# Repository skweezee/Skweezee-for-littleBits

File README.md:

# Skweezee-for-littleBits
Skweezee expansion kit for littleBits

All components of the extension kit for littleBits are available as open source hardware (licensed under CC BY-SA 4.0) and software (copyrighted by KU Leuven and licensed under MIT license).

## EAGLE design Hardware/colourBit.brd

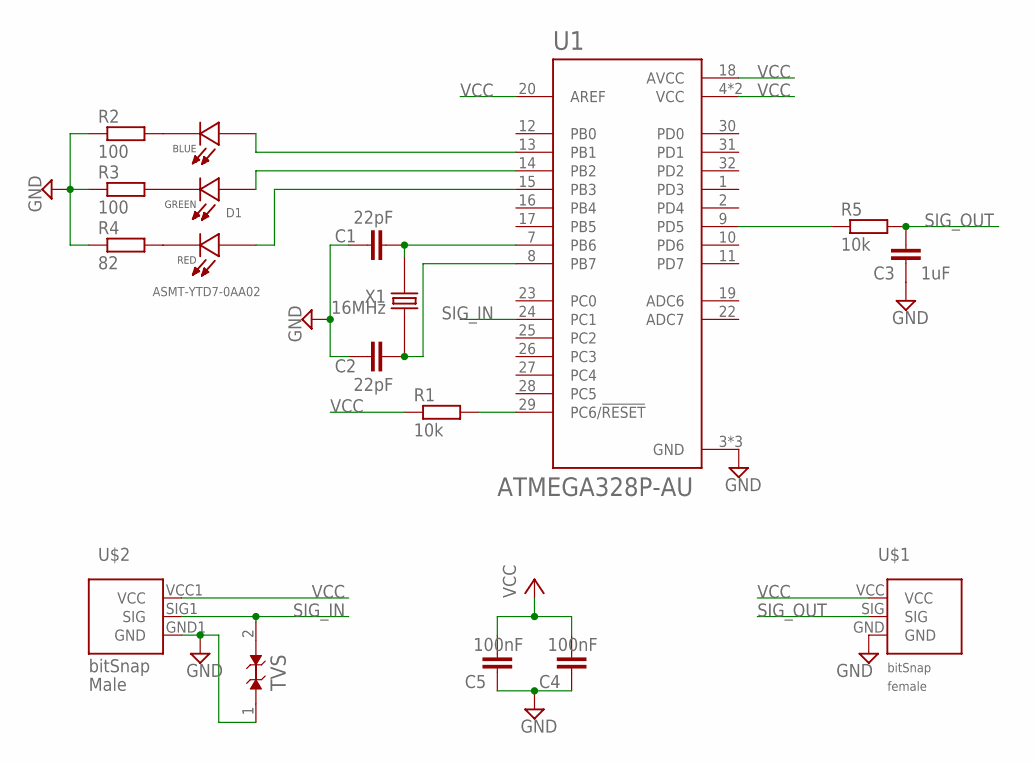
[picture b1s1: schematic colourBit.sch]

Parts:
C1, C2: 22pF; C0805
C3: 1uF; C0805
C4, C5: 100nF; C0805
D1: ASMT-YTD7-0AA02; LED_ASMT-YTD7-0AA02
R1, R5: 10k; R0805
R2, R3: 100; R0805
R4: 82; R0805
TVS: ESD9B5.0ST5G; SODFL1006X40N
U1: ATMEGA328P-AU; QFP80P900X900X120-32N
U$1: BITSNAP_V03_FEMALE
U$2: BITSNAP_V03_MALE
X1: 16MHz; XTAL500X320X120

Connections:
GND: C1.1, C2.1, C3.1, C4.1, C5.1, R2.1, R3.1, R4.1, TVS.1 (A), U1.3 (GND), U1.5 (GND), U1.21 (GND), U$1.GND, U$2.GND1 (GND)
unnamed: C1.2, U1.7 (PB6), X1.2
unnamed: C2.2, U1.8 (PB7), X1.1
unnamed: R1.2, U1.29 (PC6/!RESET)
unnamed: D1.1 (B_C), R2.2
unnamed: D1.2 (G_C), R3.2
unnamed: D1.3 (R_C), R4.2
unnamed: D1.6 (B_A), U1.13 (PB1)
unnamed: D1.5 (G_A), U1.14 (PB2)
unnamed: D1.4 (R_A), U1.15 (PB3)
unnamed: R5.1, U1.9 (PD5)
SIG_IN: TVS.2 (A1), U1.24 (PC1), U$2.SIG1 (SIG)
SIG_OUT: C3.2, R5.2, U$1.SIG
VCC: C4.2, C5.2, R1.1, U1.4 (VCC), U1.6 (VCC), U1.18 (AVCC), U1.20 (AREF), U$1.VCC, U$2.VCC1 (VCC)

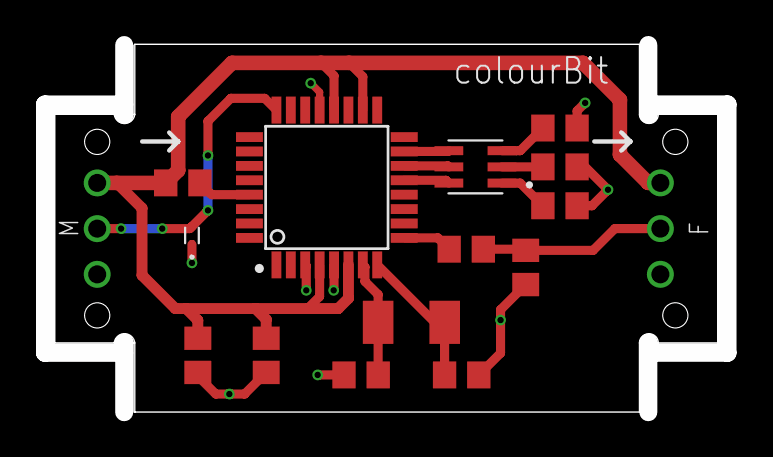
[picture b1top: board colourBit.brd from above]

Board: 2 copper layers, 37.9 x 20.4 mm, 16 parts (0 on the bottom side), 14 nets.

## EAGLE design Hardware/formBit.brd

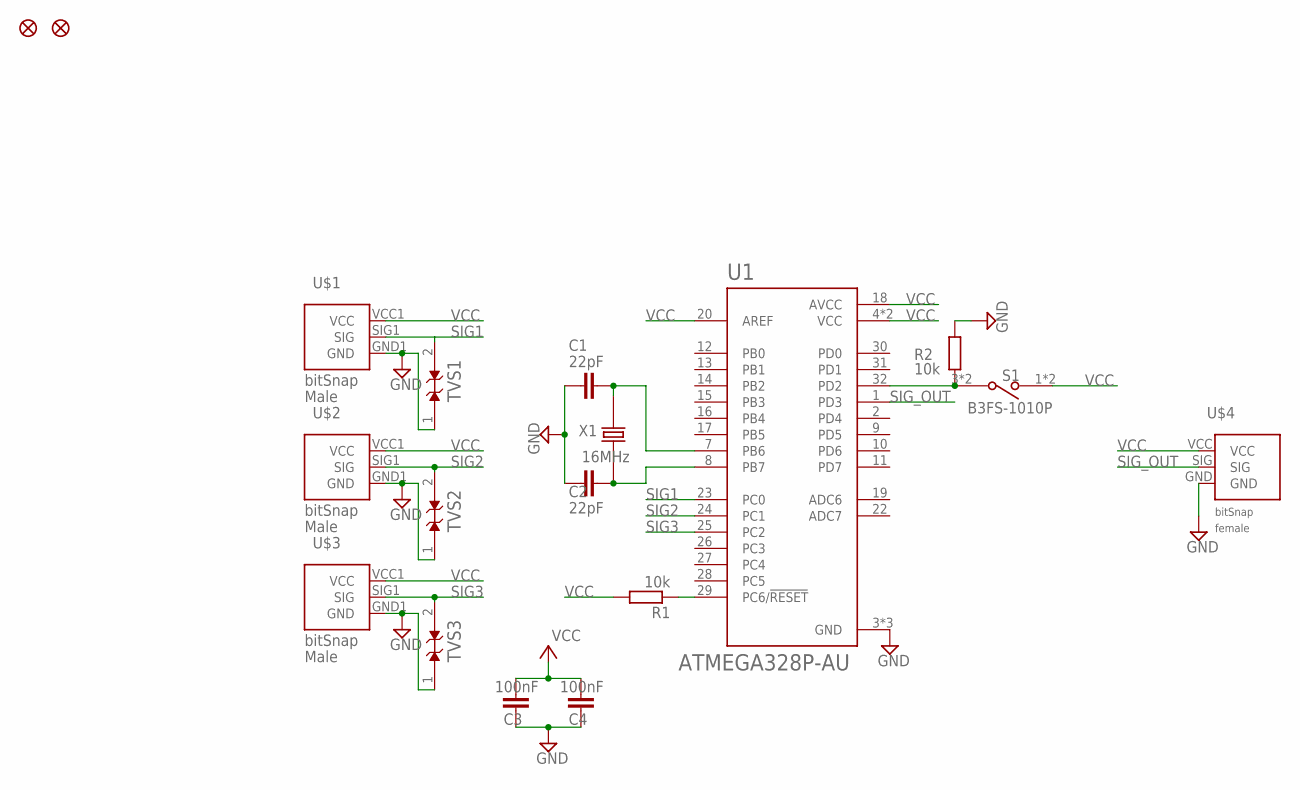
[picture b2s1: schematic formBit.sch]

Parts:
C1, C2: 22pF; C0805
C3, C4: 100nF; C0805
R1, R2: 10k; R0805
S1: B3FS-1010P; SW_B3FS-1010P
TVS1, TVS2, TVS3: ESD9B5.0ST5G; SODFL1006X40N
U1: ATMEGA328P-AU; QFP80P900X900X120-32N
U$1, U$2, U$3: BITSNAP_V03_MALE
U$4: BITSNAP_V03_FEMALE
U$5, U$6: FIDUCIAL; FIDUCIAL1X2.5
X1: 16MHz; XTAL500X320X120

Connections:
GND: C1.1, C2.1, C3.1, C4.1, R2.1, TVS1.1 (A), TVS2.1 (A), TVS3.1 (A), U1.3 (GND), U1.5 (GND), U1.21 (GND), U$1.GND1 (GND), U$2.GND1 (GND), U$3.GND1 (GND), U$4.GND
unnamed: R2.2, S1.3 (2), S1.4 (2), U1.32 (PD2)
unnamed: C2.2, U1.8 (PB7), X1.1
unnamed: C1.2, U1.7 (PB6), X1.2
unnamed: R1.1, U1.29 (PC6/!RESET)
SIG1: TVS1.2 (A1), U1.23 (PC0), U$1.SIG1 (SIG)
SIG2: TVS2.2 (A1), U1.24 (PC1), U$2.SIG1 (SIG)
SIG3: TVS3.2 (A1), U1.25 (PC2), U$3.SIG1 (SIG)
SIG_OUT: U1.1 (PD3), U$4.SIG
VCC: C3.2, C4.2, R1.2, S1.1, S1.2 (1), U1.4 (VCC), U1.6 (VCC), U1.18 (AVCC), U1.20 (AREF), U$1.VCC1 (VCC), U$2.VCC1 (VCC), U$3.VCC1 (VCC), U$4.VCC

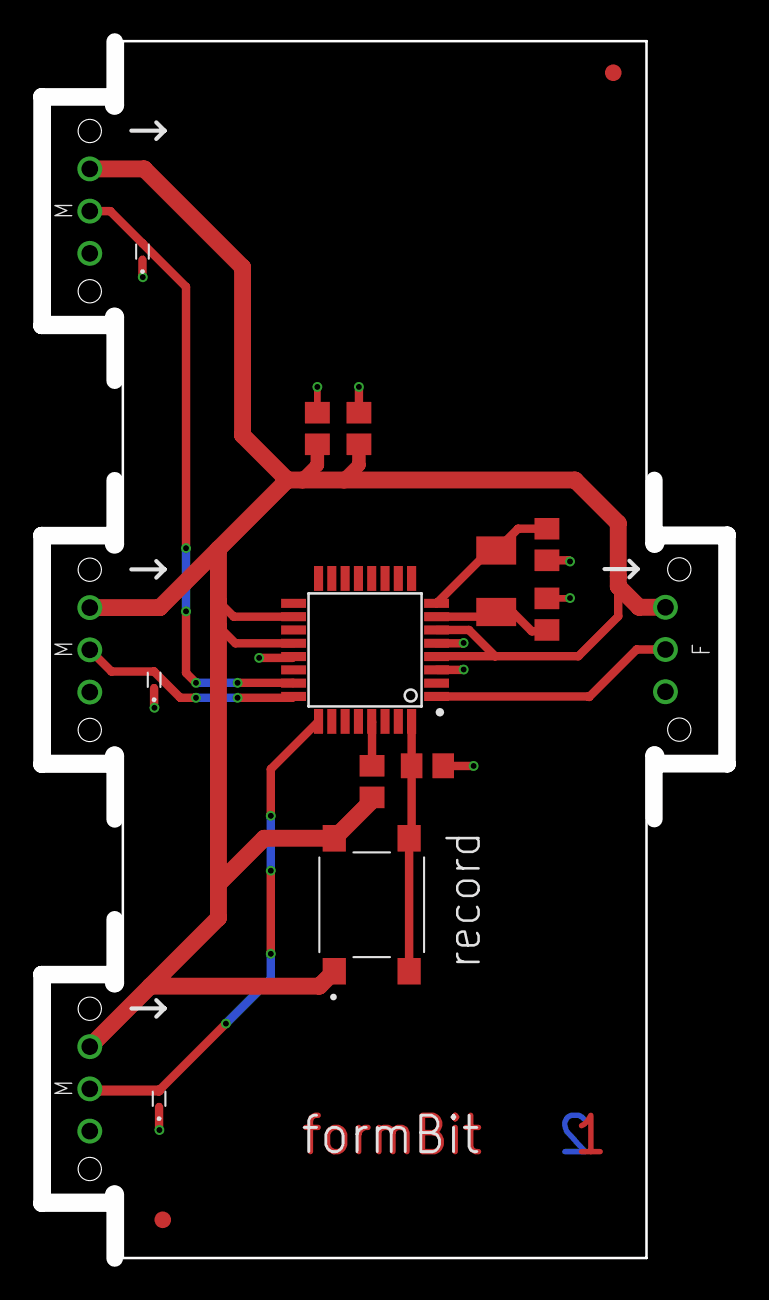
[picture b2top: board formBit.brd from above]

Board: 2 copper layers, 40.3 x 73.2 mm, 18 parts (0 on the bottom side), 10 nets.

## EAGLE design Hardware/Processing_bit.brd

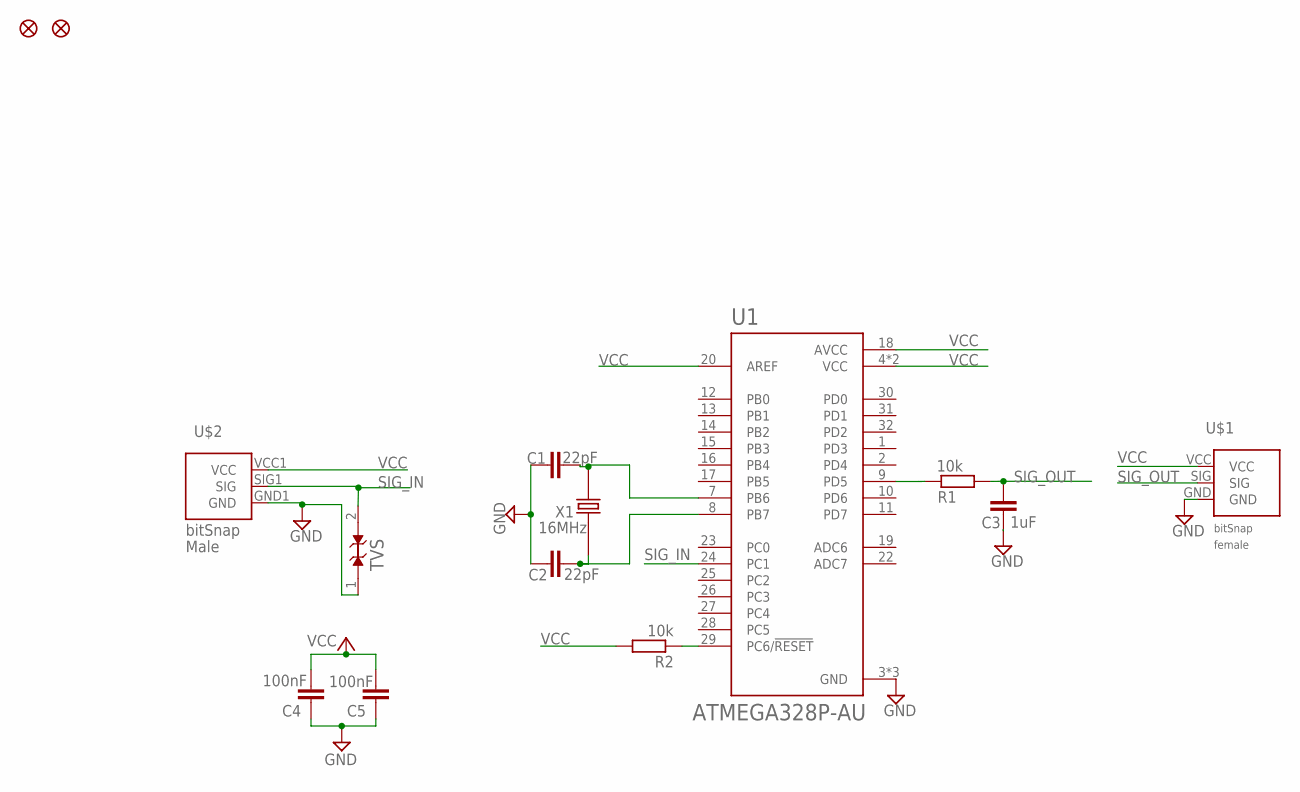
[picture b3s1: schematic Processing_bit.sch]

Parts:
C1, C2: 22pF; C0805
C3: 1uF; C0805
C4, C5: 100nF; C0805
R1, R2: 10k; R0805
TVS: ESD9B5.0ST5G; SODFL1006X40N
U1: ATMEGA328P-AU; QFP80P900X900X120-32N
U$1: BITSNAP_V03_FEMALE
U$2: BITSNAP_V03_MALE
U$3, U$4: FIDUCIAL; FIDUCIAL1X2.5
X1: 16MHz; XTAL500X320X120

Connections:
GND: C1.1, C2.1, C3.1, C4.1, C5.1, TVS.1 (A), U1.3 (GND), U1.5 (GND), U1.21 (GND), U$1.GND, U$2.GND1 (GND)
unnamed: C1.2, U1.7 (PB6), X1.2
unnamed: C2.2, U1.8 (PB7), X1.1
unnamed: R2.1, U1.29 (PC6/!RESET)
unnamed: R1.2, U1.9 (PD5)
SIG_IN: TVS.2 (A1), U1.24 (PC1), U$2.SIG1 (SIG)
SIG_OUT: C3.2, R1.1, U$1.SIG
VCC: C4.2, C5.2, R2.2, U1.4 (VCC), U1.6 (VCC), U1.18 (AVCC), U1.20 (AREF), U$1.VCC, U$2.VCC1 (VCC)

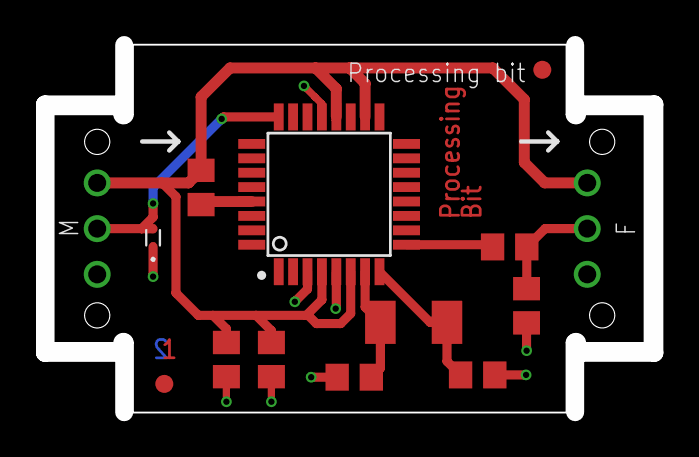
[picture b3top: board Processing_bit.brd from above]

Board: 2 copper layers, 33.9 x 20.4 mm, 14 parts (0 on the bottom side), 8 nets.

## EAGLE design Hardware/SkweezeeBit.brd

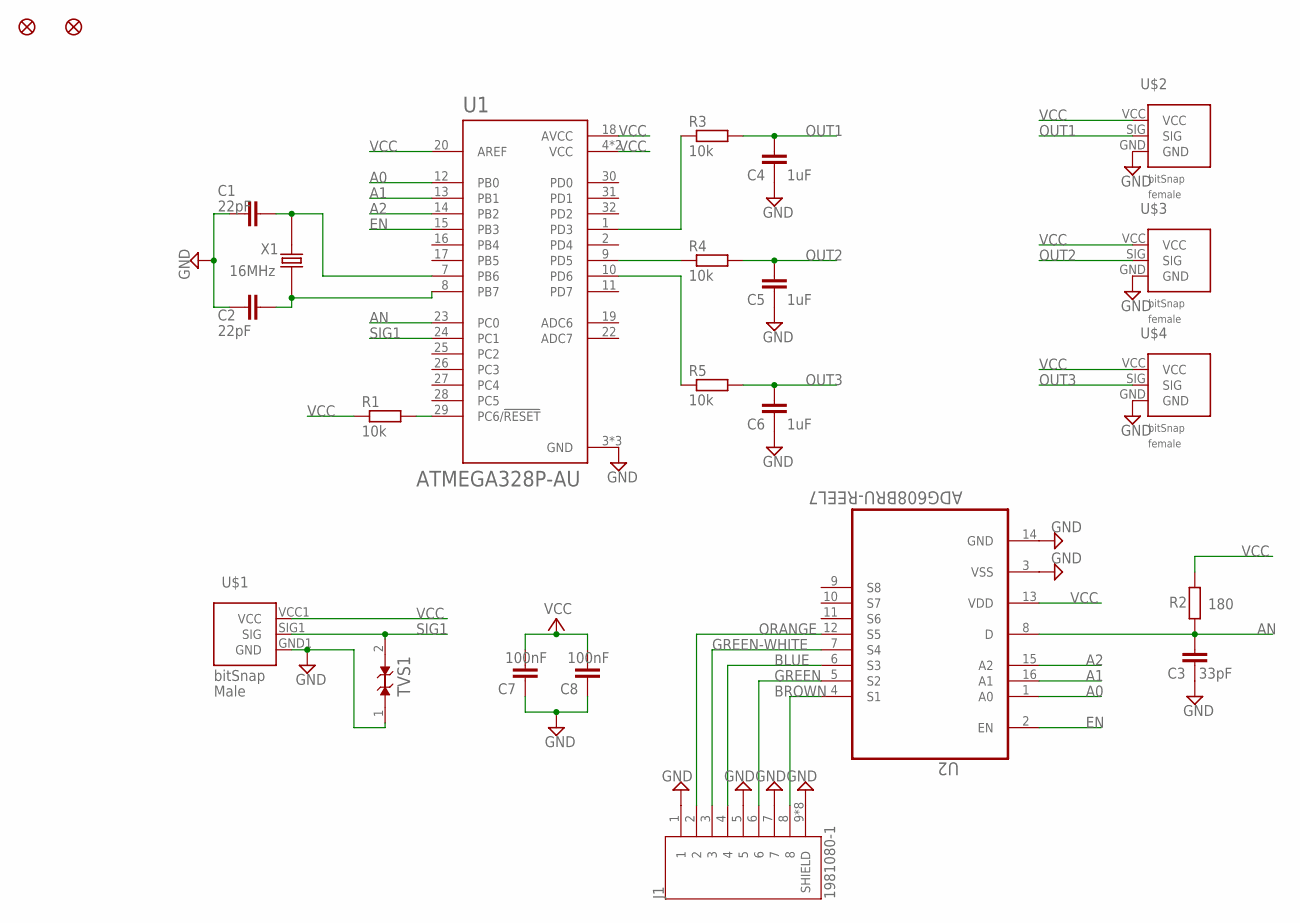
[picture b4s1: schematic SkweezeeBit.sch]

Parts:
C1, C2: 22pF; C0805
C3: 33pF; C0805
C4, C5, C6: 1uF; C0805
C7, C8: 100nF; C0805
J1: 1981080-1; CONN_1981080-1
R1, R3, R4, R5: 10k; R0805
R2: 180; R0805
TVS1: ESD9B5.0ST5G; SODFL1006X40N
U1: ATMEGA328P-AU; QFP80P900X900X120-32N
U2: ADG608BRU-REEL7; SOP65P640X120-16N
U$1: BITSNAP_V03_MALE
U$2, U$3, U$4: BITSNAP_V03_FEMALE
U$5, U$6: FIDUCIAL; FIDUCIAL1X2.5
X1: 16MHz; XTAL500X320X120

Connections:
A0: U1.12 (PB0), U2.1 (A0)
A1: U1.13 (PB1), U2.16 (A1)
A2: U1.14 (PB2), U2.15 (A2)
AN: C3.2, R2.1, U1.23 (PC0), U2.8 (D)
BLUE: J1.4, U2.6 (S3)
BROWN: J1.8, U2.4 (S1)
EN: U1.15 (PB3), U2.2 (EN)
GND: C1.1, C2.1, C3.1, C4.1, C5.1, C6.1, C7.1, C8.1, J1.1, J1.5, J1.7, J1.9 (SHIELD), J1.9.1 (SHIELD), J1.10 (SHIELD), J1.10.1 (SHIELD), J1.11 (SHIELD), J1.12 (SHIELD), J1.13 (SHIELD), J1.13.1 (SHIELD), TVS1.1 (A), U1.3 (GND), U1.5 (GND), U1.21 (GND), U2.3 (VSS), U2.14 (GND), U$1.GND1 (GND), U$2.GND, U$3.GND, U$4.GND
GREEN: J1.6, U2.5 (S2)
GREEN-WHITE: J1.3, U2.7 (S4)
unnamed: C2.2, U1.8 (PB7), X1.2
unnamed: C1.2, U1.7 (PB6), X1.1
unnamed: R1.2, U1.29 (PC6/!RESET)
unnamed: R3.1, U1.1 (PD3)
unnamed: R4.1, U1.9 (PD5)
unnamed: R5.1, U1.10 (PD6)
ORANGE: J1.2, U2.12 (S5)
OUT1: C4.2, R3.2, U$2.SIG
OUT2: C5.2, R4.2, U$3.SIG
OUT3: C6.2, R5.2, U$4.SIG
SIG1: TVS1.2 (A1), U1.24 (PC1), U$1.SIG1 (SIG)
VCC: C7.2, C8.2, R1.1, R2.2, U1.4 (VCC), U1.6 (VCC), U1.18 (AVCC), U1.20 (AREF), U2.13 (VDD), U$1.VCC1 (VCC), U$2.VCC, U$3.VCC, U$4.VCC

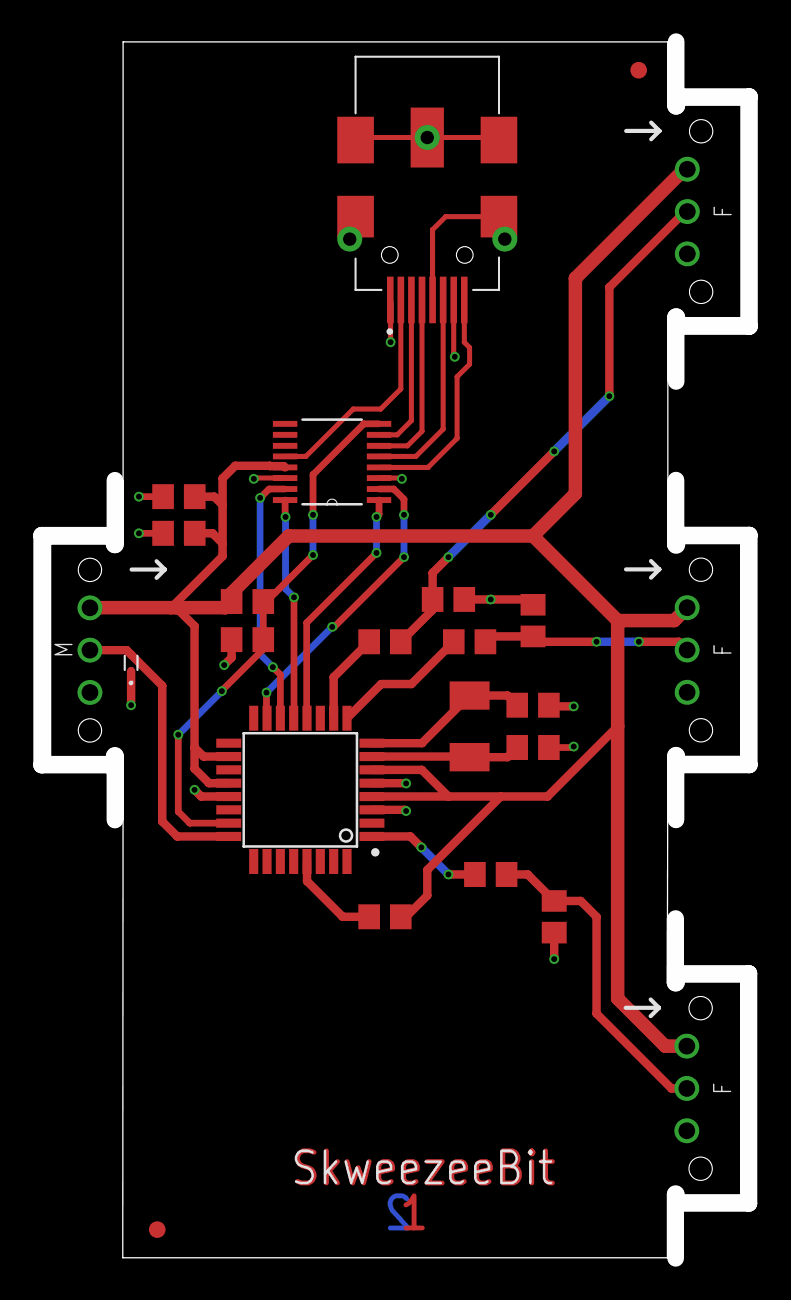
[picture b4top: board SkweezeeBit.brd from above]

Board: 2 copper layers, 42.5 x 73.0 mm, 24 parts (0 on the bottom side), 22 nets.

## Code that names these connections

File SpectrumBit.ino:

typedef struct {
    double r;       // a fraction between 0 and 1
    double g;       // a fraction between 0 and 1
    double b;       // a fraction between 0 and 1
} rgb;

typedef struct {
    double h;       // angle in degrees
    double s;       // a fraction between 0 and 1
    double v;       // a fraction between 0 and 1
} hsv;

static hsv   rgb2hsv(rgb in);
static rgb   hsv2rgb(hsv in);

void setup() {
  Serial.begin(9600); // baud rate 9600 bps
  TCCR2B = (TCCR2B & 0b11111000) | 0x03;
}

void loop() {
  int valHue = analogRead(PC0)>>2;
  int valSaturation = analogRead(PC1)>>2;
  int valValue = analogRead(PC2)>>2;
        
  //Do processing
  hsv input;
  input.h = double(valHue);
  input.s = double(valSaturation) / 255;
  input.v = double(valValue) / 255;
  rgb result = hsv2rgb(input);
  
  delay(10);

  analogWrite(9, (result.b*255)); 
  analogWrite(10, (result.g*255));
  analogWrite(11, (result.r*255));
  analogWrite(PD6, valHue);
  analogWrite(PD5, valSaturation);
  analogWrite(PD3, valValue);
}

//Code voor de omzetting van HSV(B) naar RGB:
//https://stackoverflow.com/questions/3018313/algorithm-to-convert-rgb-to-hsv-and-hsv-to-rgb-in-range-0-255-for-both
rgb hsv2rgb(hsv in)
{
    double      hh, p, q, t, ff;
    long        i;
    rgb         out;

    if(in.s <= 0.0) {       // < is bogus, just shuts up warnings
        out.r = in.v;
        out.g = in.v;
        out.b = in.v;
        return out;
    }
    hh = in.h;
    if(hh >= 360.0) hh = 0.0;
    hh /= 60.0;
    i = (long)hh;
    ff = hh - i;
    p = in.v * (1.0 - in.s);
    q = in.v * (1.0 - (in.s * ff));
    t = in.v * (1.0 - (in.s * (1.0 - ff)));

    switch(i) {
    case 0:
        out.r = in.v;
        out.g = t;
        out.b = p;
        break;
    case 1:
        out.r = q;
        out.g = in.v;
        out.b = p;
        break;
    case 2:
        out.r = p;
        out.g = in.v;
        out.b = t;
        break;

    case 3:
        out.r = p;
        out.g = q;
        out.b = in.v;
        break;
    case 4:
        out.r = t;
        out.g = p;
        out.b = in.v;
        break;
    case 5:
    default:
        out.r = in.v;
        out.g = p;
        out.b = q;
        break;
    }
    return out;     
}

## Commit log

2020-06-12 Update LICENSE
2020-08-31 Create Hardware
2020-08-31 Create Video
